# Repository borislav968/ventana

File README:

This folder contains the crank power window controller firmware source code and PCB design.

This controller replaces the crank window mechanism and is intended to be applied in retro cars where the owner
doesn't want to install the buttons when installing the power window drive.

The main features are:
- soft motor start and stop.
- full opening or closing mode without holding the lever.
- an input from the car alarm or central lock system for closing the windows.
- protection from motor overload or short circuit with a current sensor.
- protection from output short circuit to the ground or battery.

© Boris Malkov 2019

This program is free software: you can redistribute it and/or modify
    it under the terms of the GNU General Public License as published by
    the Free Software Foundation, either version 3 of the License, or
    (at your option) any later version.

    This program is distributed in the hope that it will be useful,
    but WITHOUT ANY WARRANTY; without even the implied warranty of
    MERCHANTABILITY or FITNESS FOR A PARTICULAR PURPOSE.  See the
    GNU General Public License for more details.

    You should have received a copy of the GNU General Public License
    along with this program.  If not, see <https://www.gnu.org/licenses/>.

В этой папке находятся исходные тексты ПО и чертежи печатной платы контроллера электростеклоподъёмника.

Контроллер устанавливается на место штатного механизма ручного стеклоподъёмника и использует его поворотную рукоятку,
прездназначен для установки на ретро-автомобили, где использование кнопок неуместно.

Основные функции:
- плавный пуск и остановка двигателя привода.
- доводка до полного открытия и закрытия без удерживания рукоятки.
- вход для подключения к охранной системе или центральному замку для закрытия окон.
- зашита от перегрузки или КЗ электродвигателя.
- защита от замыкания выходов на массу или плюсовой провод.

© Борис Мальков 2019

Это свободная программа: вы можете перераспространять ее и/или изменять
   ее на условиях Стандартной общественной лицензии GNU в том виде, в каком
   она была опубликована Фондом свободного программного обеспечения; либо
   версии 3 лицензии, либо (по вашему выбору) любой более поздней версии.

   Эта программа распространяется в надежде, что она будет полезной,
   но БЕЗО ВСЯКИХ ГАРАНТИЙ; даже без неявной гарантии ТОВАРНОГО ВИДА
   или ПРИГОДНОСТИ ДЛЯ ОПРЕДЕЛЕННЫХ ЦЕЛЕЙ. Подробнее см. в Стандартной
   общественной лицензии GNU.

   Вы должны были получить копию Стандартной общественной лицензии GNU
   вместе с этой программой. Если это не так, см.
   <https://www.gnu.org/licenses/>.

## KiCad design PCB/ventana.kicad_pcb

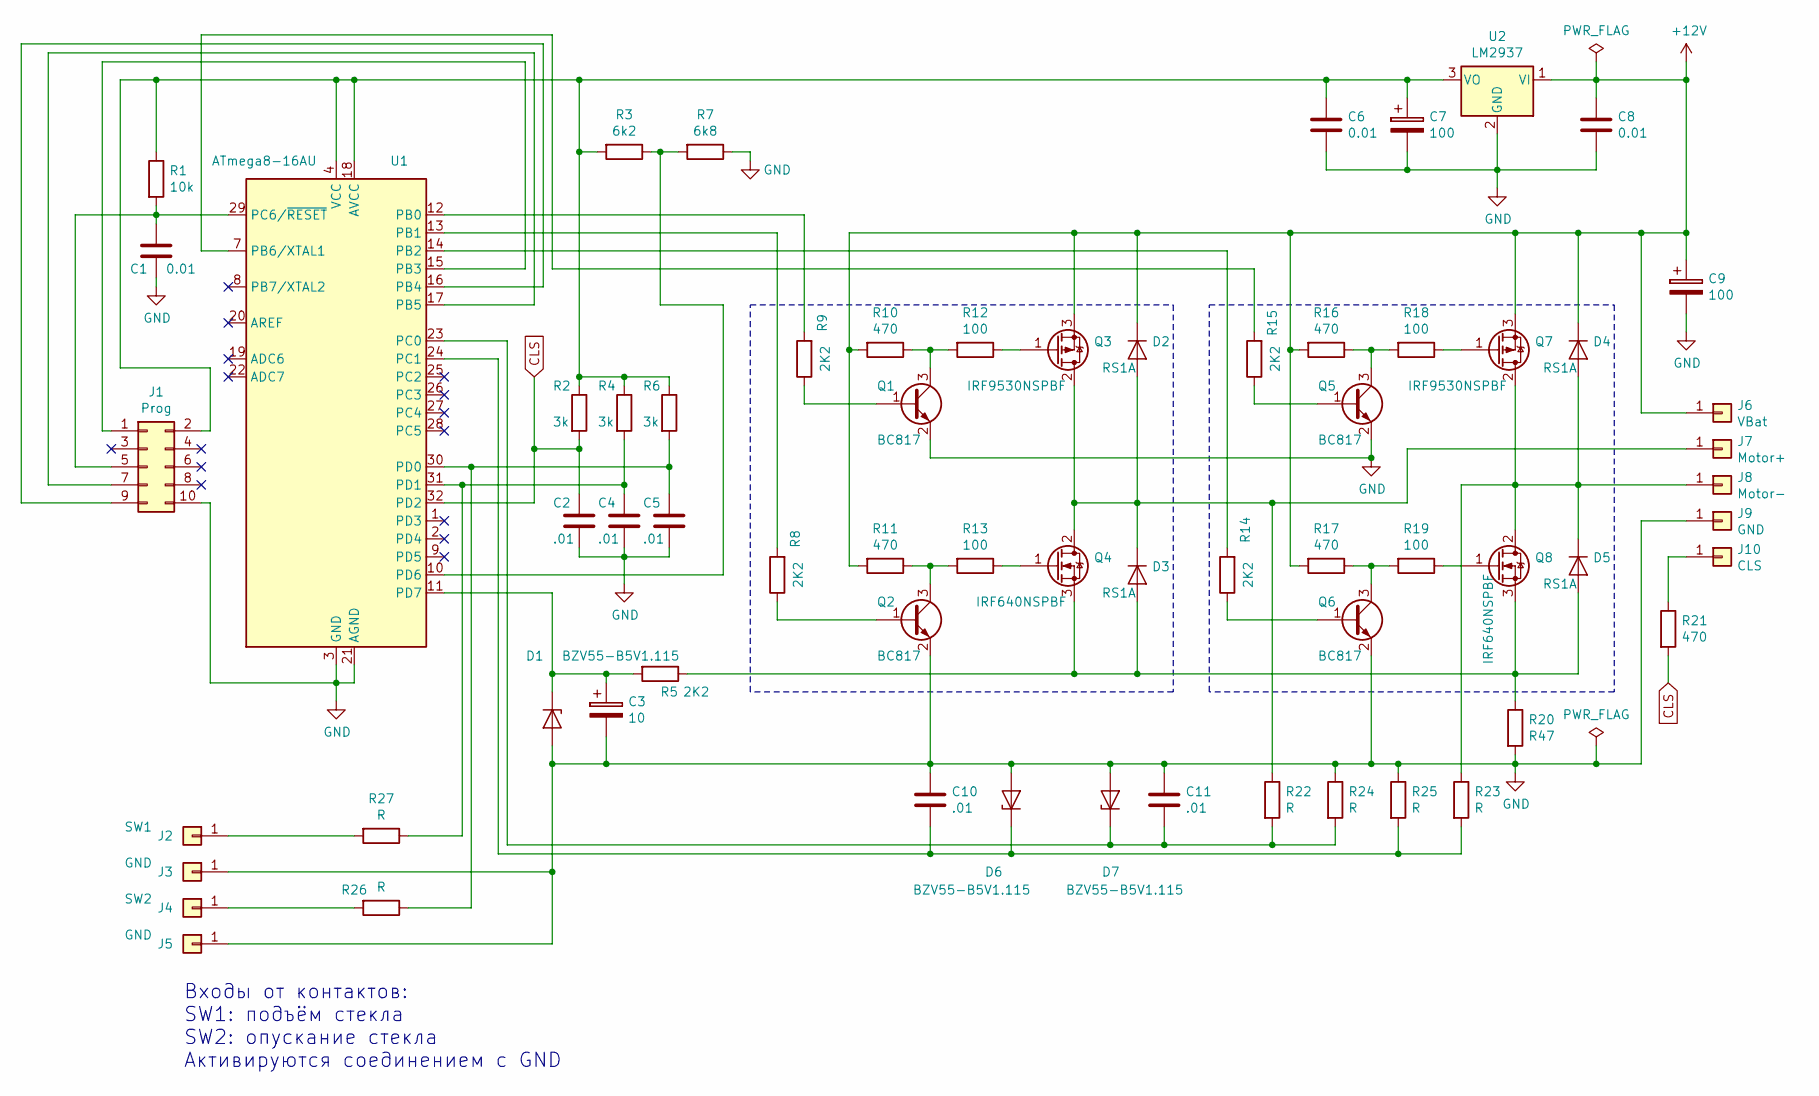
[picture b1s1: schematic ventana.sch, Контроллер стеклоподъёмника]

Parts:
C1, C6, C8: 0.01; C_1206_3216Metric
C2, C4, C5, C10, C11: .01; C_1206_3216Metric
C3: 10; CP_Elec_5x5.3
C7, C9: 100; CP_Elec_8x6.9
D1, D6, D7: BZV55-B5V1.115; D_SOD-123
D2, D3, D4, D5: RS1A; D_SMA
J1: Prog; conn_2_5
J2: SW1; PinHeader_1x01_P2.54mm_Vertical
J3, J5, J9: GND; PinHeader_1x01_P2.54mm_Vertical
J4: SW2; PinHeader_1x01_P2.54mm_Vertical
J6: VBat; PinHeader_1x01_P2.54mm_Vertical
J7: Motor+; PinHeader_1x01_P2.54mm_Vertical
J8: Motor-; PinHeader_1x01_P2.54mm_Vertical
J10: CLS; PinHeader_1x01_P2.54mm_Vertical
Q1, Q2, Q5, Q6: BC817; SOT-23
Q3, Q7: IRF9530NSPBF; TO-263-2
Q4, Q8: IRF640NSPBF; TO-263-2
R1: 10k; R_1206_3216Metric
R2, R4, R6: 3k; R_1206_3216Metric
R3: 6k2; R_1206_3216Metric
R5, R8, R9, R14, R15: 2K2; R_1206_3216Metric
R7: 6k8; R_1206_3216Metric
R10, R11, R16, R17, R21: 470; R_1206_3216Metric
R12, R13, R18, R19: 100; R_1206_3216Metric
R20: R47; R_Axial_Power_L25.0mm_W9.0mm_P30.48mm
R22, R23, R24, R25, R26, R27: R; R_1206_3216Metric
U1: ATmega8-16AU; AtMega8_TQFP32
U2: LM2937; SOT-223

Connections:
+12V: C8.1, C9.1, D2.1 (K), D4.1 (K), J6.1, Q3.3 (S), Q7.3 (S), R10.2, R11.2, R16.2, R17.2, U2.1 (VI)
CLS: C2.1, R2.2, R21.2, U1.32 (PD2)
GND: C1.2, C2.2, C3.2, C4.2, C5.2, C6.2, C7.2, C8.2, C9.2, C10.1, C11.1, D1.2 (A), D6.2 (A), D7.2 (A), J1.10, J3.1, J5.1, J9.1, Q1.2 (E), Q2.2 (E), Q5.2 (E), Q6.2 (E), R7.1, R20.2, R24.1, R25.1, U1.3 (GND), U1.5 (GND), U1.21 (AGND), U2.2 (GND)
unnamed: C1.1, J1.5, R1.2, U1.29 (PC6/~RESET)
unnamed: C3.1, D1.1 (K), R5.2, U1.11 (PD7)
unnamed: C4.1, R4.2, R27.1, U1.31 (PD1)
unnamed: C5.1, R6.2, R26.1, U1.30 (PD0)
unnamed: C6.1, C7.1, J1.2, R1.1, R2.1, R3.2, R4.1, R6.1, U1.4 (VCC), U1.6 (VCC), U1.18 (AVCC), U2.3 (VO)
unnamed: C10.2, D6.1 (K), R23.2, R25.2, U1.24 (PC1)
unnamed: C11.2, D7.1 (K), R22.2, R24.2, U1.23 (PC0)
unnamed: D2.2 (A), D3.1 (K), J7.1, Q3.2 (D), Q4.2 (D), R22.1
unnamed: D3.2 (A), D5.2 (A), Q4.3 (S), Q8.3 (S), R5.1, R20.1
unnamed: D4.2 (A), D5.1 (K), J8.1, Q7.2 (D), Q8.2 (D), R23.1
unnamed: J1.1, U1.15 (PB3)
unnamed: J1.7, U1.17 (PB5)
unnamed: J1.9, U1.16 (PB4)
unnamed: J2.1, R27.2
unnamed: J4.1, R26.2
unnamed: J10.1, R21.1
unnamed: Q1.1 (B), R9.1
unnamed: Q1.3 (C), R10.1, R12.2
unnamed: Q2.1 (B), R8.1
unnamed: Q2.3 (C), R11.1, R13.2
unnamed: Q3.1 (G), R12.1
unnamed: Q4.1 (G), R13.1
unnamed: Q5.1 (B), R15.1
unnamed: Q5.3 (C), R16.1, R18.2
unnamed: Q6.1 (B), R14.1
unnamed: Q6.3 (C), R17.1, R19.2
unnamed: Q7.1 (G), R18.1
unnamed: Q8.1 (G), R19.1
unnamed: R3.1, R7.2, U1.10 (PD6)
unnamed: R8.2, U1.13 (PB1)
unnamed: R9.2, U1.12 (PB0)
unnamed: R14.2, U1.14 (PB2)
unnamed: R15.2, U1.7 (PB6/XTAL1)

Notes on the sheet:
Входы от контактов: SW1: подъём стекла SW2: опускание стекла Активируются соединением с GND

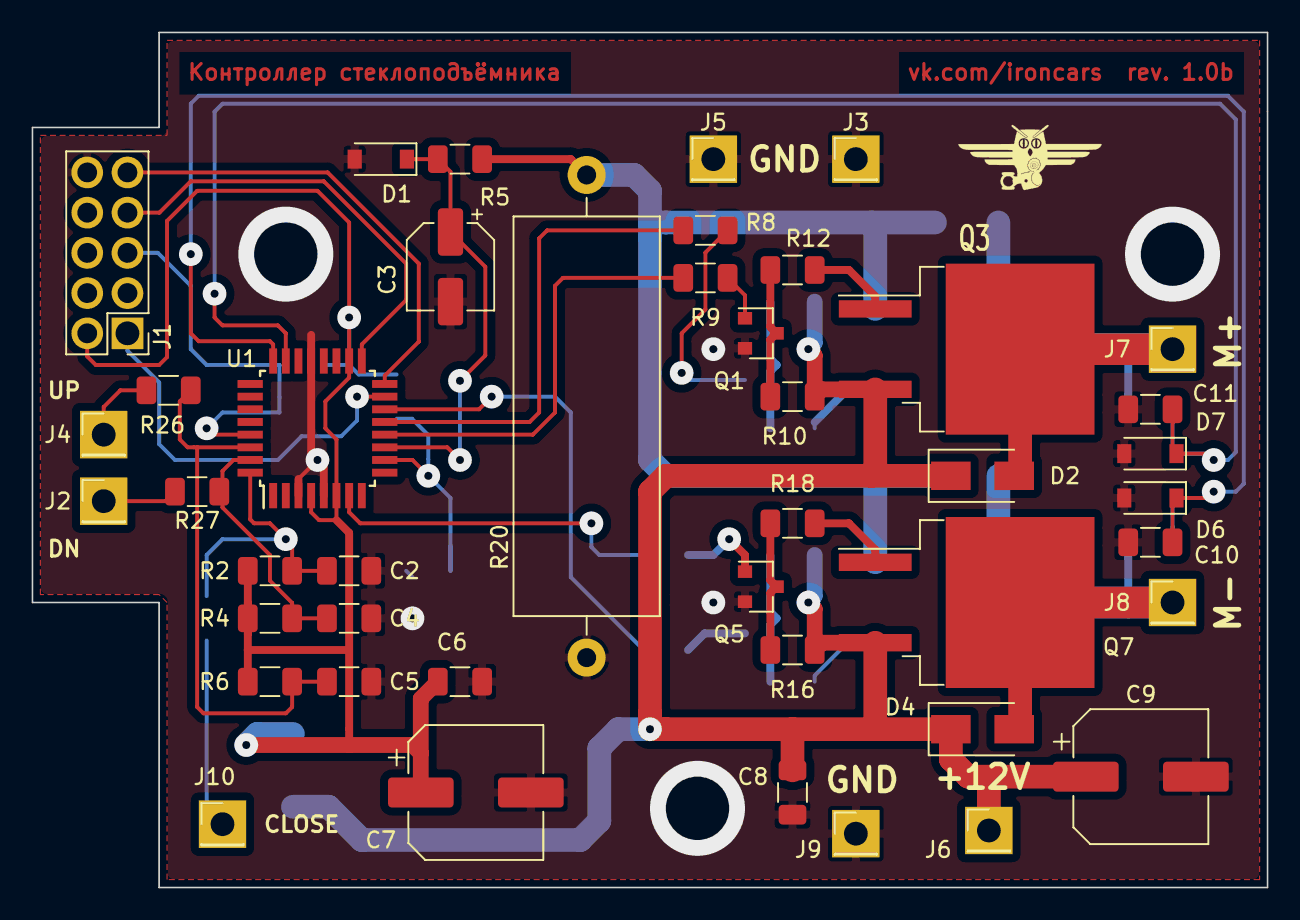
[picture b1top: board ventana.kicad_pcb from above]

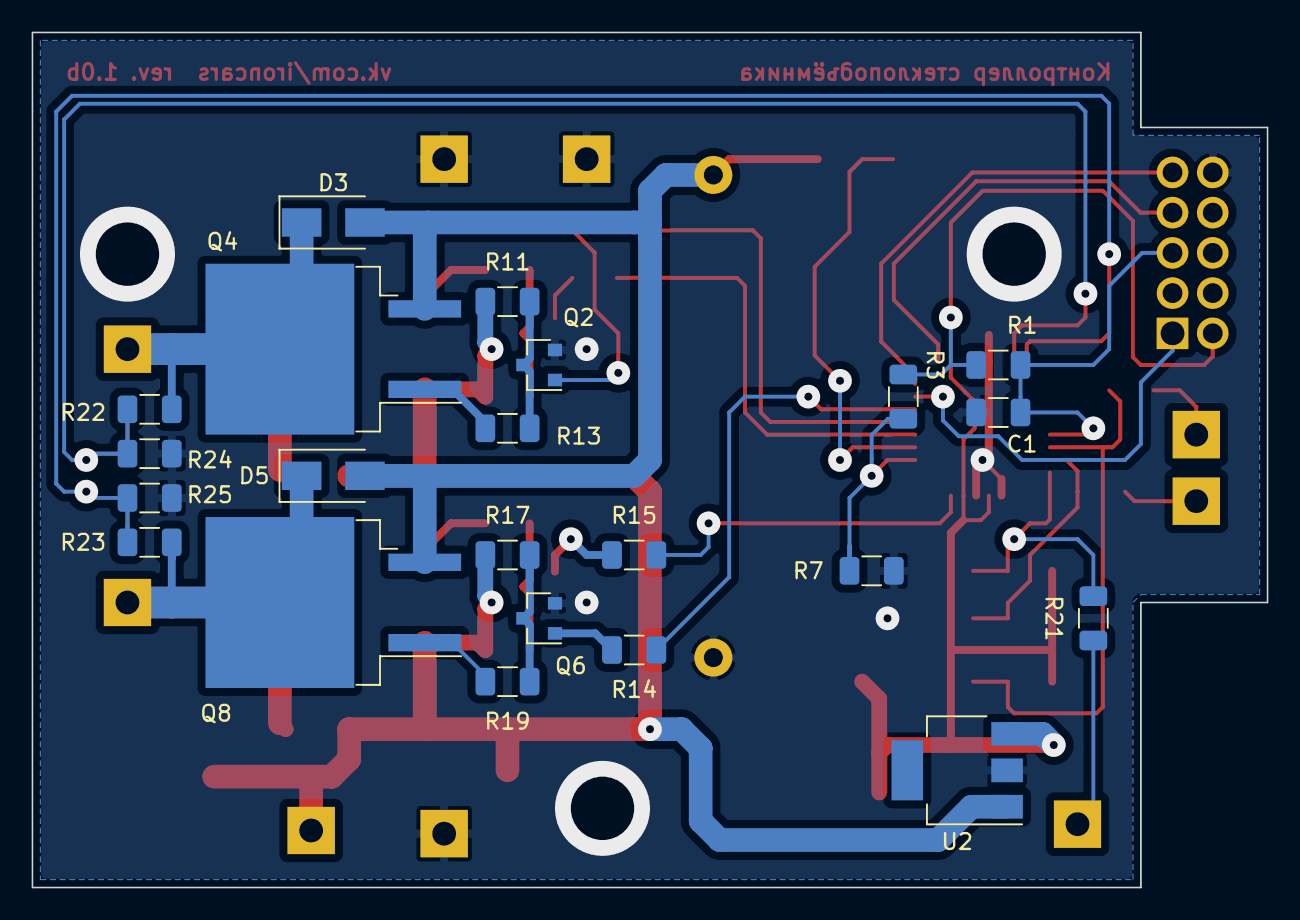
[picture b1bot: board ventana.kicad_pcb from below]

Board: 2 copper layers, 78.0 x 54.0 mm, 65 parts (22 on the bottom side), 36 nets.

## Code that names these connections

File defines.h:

/*
 * defines.h
 *
 * Created on: 27 сент. 2018 г.
 *      Author: Borislav Malkov
 */

#ifndef DEFINES_H
#define DEFINES_H

#define uchar   unsigned char
#define uint    unsigned int

#define ON          0x01
#define OFF         0x00

#define ST_MOVE     (1<<0)
#define ST_DIR      (1<<1)
#define ST_HOLD     (1<<2)
#define ST_EDGE     (1<<3)
#define ST_SPDUP    (1<<4)
#define ST_TMOUT    (1<<5)
#define ST_LEARN    (1<<6)
#define ST_BACK     (1<<7)

#define CMD_UP      (1<<0)
#define CMD_DN      (1<<1)
#define CMD_HOLD    (CMD_UP | CMD_DN)
#define CMD_CLOSE   (1<<2)

#define BR_LR       0
#define BR_UR       1
#define BR_LL       2
#define BR_UL       3
#define BR_ERROR    0b11110000

#if defined __AVR_ATmega8__
    #define SW_PORT     PORTD
    #define SW_DDR      DDRD
    #define SW_PIN      PIND
    #define SW_0        PD0
    #define SW_1        PD1
    #define SW_2        PD2
    #define MT_PORT     PORTB
    #define MT_DDR      DDRB
    #define MT_PIN      PINB
    #define MT_UL       PB0
    #define MT_UR       PB6
    #define MT_LL       PB1
    #define MT_LR       PB2
    #define CMP_PORT    PORTD
    #define CMP_DDR     DDRD
    #define AIN0        PD6
    #define AIN1        PD7
    #define PORT_ADC    PORTC
    #define DDR_ADC     DDRC
    #define ADC_L       PC0
    #define ADC_R       PC1
# else
    #error "This source is for atmega8 and atmega16 MCUs"
#endif

// motor run max duration, ~seconds
#define T_DURATION 15
#define T_MIN_DURATION 1

// PWM resolution - the bigger it is, the lower will be PWM frequency.
// Freq = F_CPU/N*(PWM_RES+1) = 8000000 / 8 * (63 + 1) = 15625Hz
// Also affects spinup/spindown time
#define PWM_RES 0x3F

// Max output voltage measured by ADC
#define MAX_VOLTAGE 170

// For short circuit protection functions
#define LO_THRESHOLD 20
#define HI_THRESHOLD 50

#define REC_LG 50

typedef uchar record[REC_LG];

typedef struct {
    uchar start;
    uchar end;
} interval;


#endif

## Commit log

2018-10-06 PWM motor control implemented
2018-10-06 Motor smooth stopping at input signal change
2018-10-09 Atmega16 support added + more comments.
2018-10-09 Moar comments.
2018-10-09 Add fuses support in code
2018-10-09 Add fuses support in makefile
2018-10-09 Input port definitions for atmega16
2018-10-10 Added defines for motor driver pins
2018-10-10 Changed PWM duty control timer0 mode
2018-10-10 Ugly switch debouncing added - to be rewritten
2018-10-10 Motor spinup time now in defines.h
2018-10-10 Some debugging
2018-10-10 Now motor restarts when the same direction activated during spindown
2018-10-10 Better debouncing routine
2018-10-11 Comparator set up
2018-12-02 Increased PWM frequency to 15625Hz
2018-12-14 Now working on atmega8
2018-12-15 Now lower MOSFETs are open when idle to improve energy saving
2018-12-15 Add KiCAD PCB project
2018-12-16 Fixed a mistake in the schematic
2018-12-16 Oops...
2018-12-16 Better motor timings
2018-12-16 Moar energy saving - noow 10mA on idle
2018-12-16 Removed all init functions for motor module
2018-12-17 ST_HOLD flag clear added
2018-12-17 Added changing of switch direction with saving in EEPROM
2018-12-17 Added new function of closing the window from additional input line
2018-12-17 Oops... ))
2018-12-17 Added some comments and minor changes
2018-12-17 Some energy saving added. Now draws only 9mA on idle
2018-12-17 Load voltage sense circuits added to schematic
2018-12-18 Schematic and PCB
2018-12-18 Add protection from short circuit outputs to ground
2018-12-18 Little correction
2018-12-21 Bridge driver module added
2018-12-22 Bridge driver module now has all planned protection
2018-12-23 Turning off transistors must occur before turning on the others
2018-12-23 AVR ISP MkII
2018-12-24 Improved voltage control
2018-12-24 Changed F_CPU from 1MHz to 8MHz
2018-12-24 More convenient bridge_update call
2018-12-24 Some comments added
2018-12-24 Added parts for midpoints voltage measurement
2019-01-01 Readme and GPL files added
2019-01-21 PCB rev 1.0b
2019-01-30 Pins redefined for the new PCB design
2019-02-11 Timing adjustments etc.
2019-02-18 Minor changes
2019-02-24 Rollback function added & some debugging made
2019-04-22 Debugging
2019-04-24 Add comments & more debug
2019-04-24 Tweaking
2019-04-24 Experimental hardness calculation by slope
2019-04-29 Works correctly, installed on 965i
